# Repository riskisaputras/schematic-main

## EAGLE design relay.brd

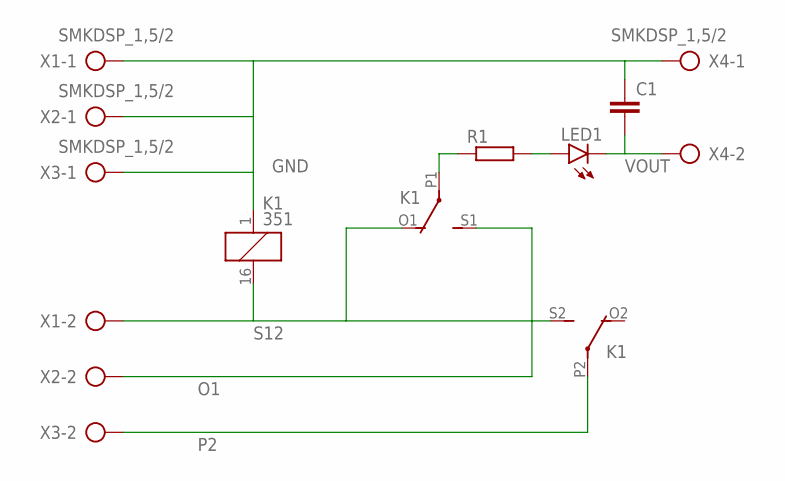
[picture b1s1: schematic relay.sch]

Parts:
C1: C-EU025-025X050; C025-025X050
K1: 351
LED1: LED3MM
R1: R-EU_0207/10; 0207/10
X1, X2, X3, X4: SMKDSP_1,5/2

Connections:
GND: C1.1, K1.1, X1.1, X2.1, X3.1, X4.1
unnamed: K1.P1, R1.1
unnamed: LED1.A, R1.2
O1: K1.S1 (S), X2.2
P2: K1.P2, X3.2
S12: K1.16 (2), K1.O1 (O), K1.S2 (S), X1.2
VOUT: C1.2, LED1.K (C), X4.2

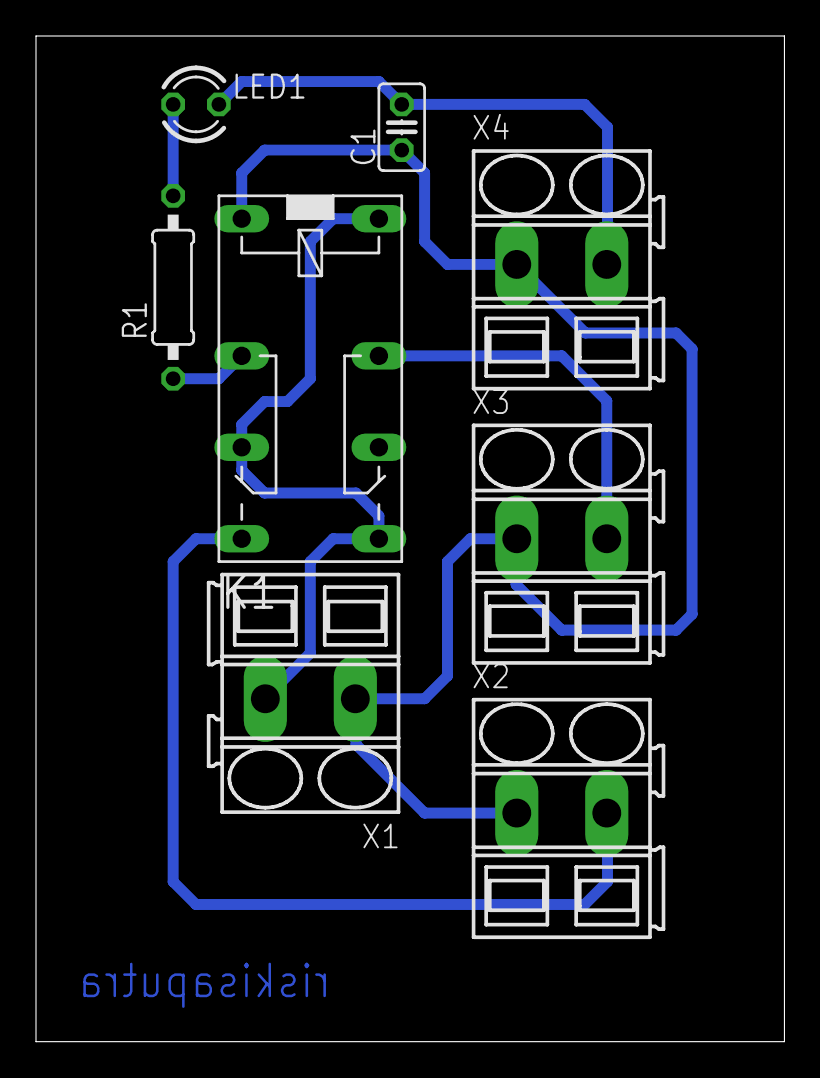
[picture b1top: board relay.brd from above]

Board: 2 copper layers, 41.6 x 55.9 mm, 8 parts (0 on the bottom side), 7 nets.

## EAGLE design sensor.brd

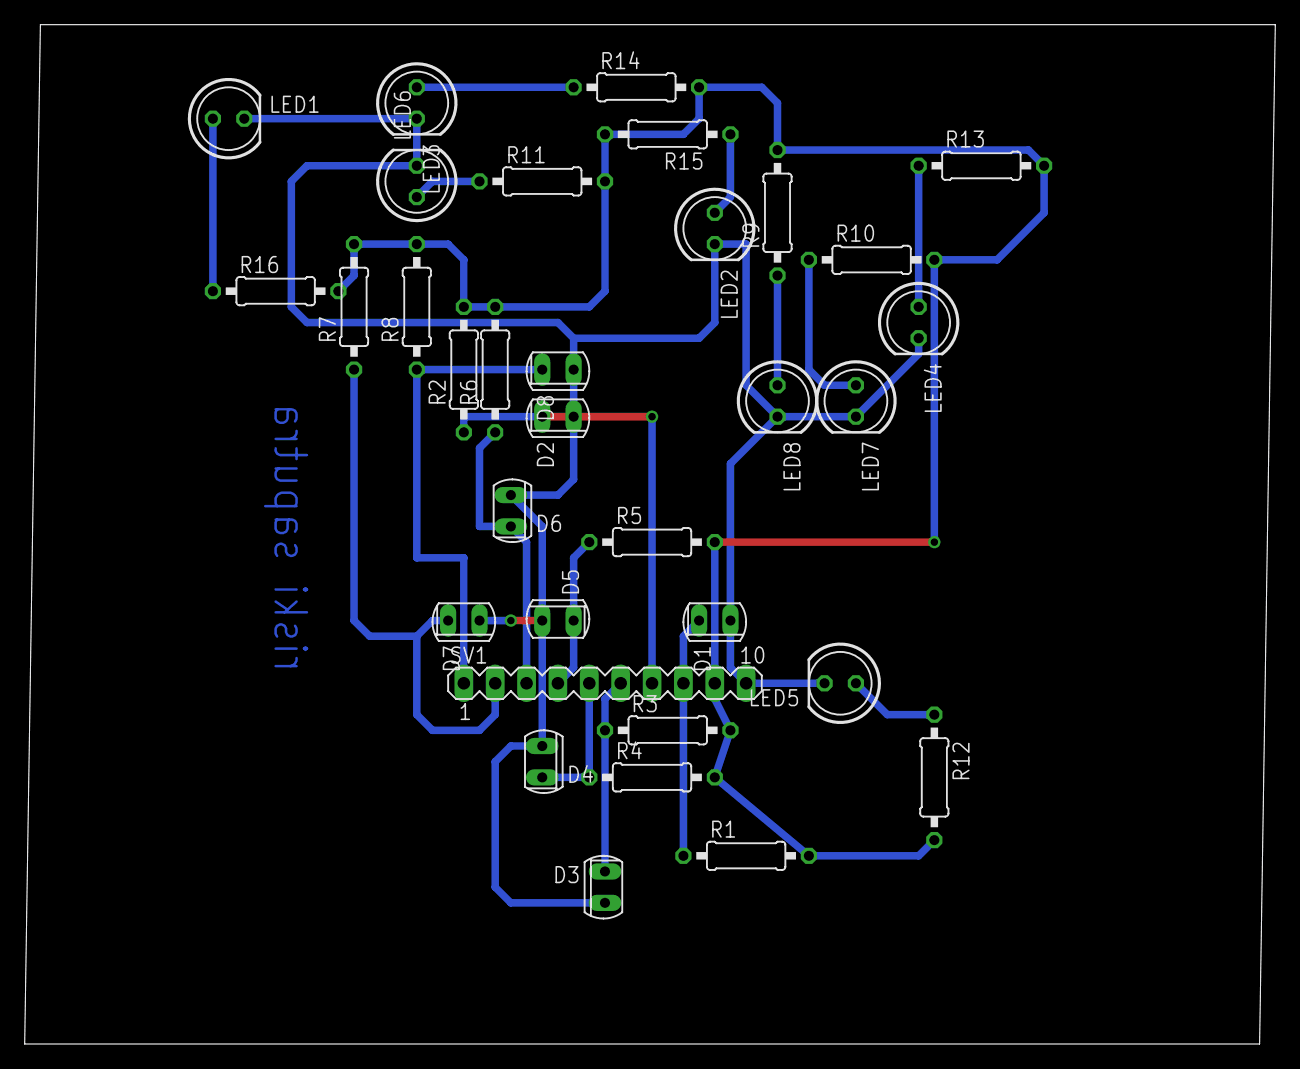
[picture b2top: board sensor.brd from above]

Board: 2 copper layers, 101.3 x 82.5 mm, 33 parts (0 on the bottom side), 18 nets.

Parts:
D1, D2, D3, D4, D5, D6, D7, D8: PhotoDioda; SFH225
LED1, LED2, LED3, LED4, LED5, LED6, LED7, LED8: LED putih SB; LED5MM
R1, R2, R3, R4, R5, R6, R7, R8: 0207/10
R9, R10, R11, R12, R13, R14, R15, R16: 330; 0207/10
SV1: MA10-1

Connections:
GND: D1.A, D2.A, D3.A, D4.A, D5.A, D6.A, D7.A, D8.A, LED1.K, LED2.K, LED3.K, LED4.K, LED5.K, LED6.K, LED7.K, LED8.K, SV1.10
unnamed: LED7.A, R10.1
unnamed: D7.K, R7.1, SV1.2
unnamed: D8.K, R8.1, SV1.1
unnamed: D1.K, R1.1, SV1.8
unnamed: D2.K, R2.1, SV1.7
unnamed: D3.K, R3.1, SV1.6
unnamed: D5.K, R5.1, SV1.4
unnamed: D4.K, R4.1, SV1.5
unnamed: D6.K, R6.1, SV1.3
unnamed: LED6.A, R11.1
unnamed: LED5.A, R12.1
unnamed: LED4.A, R13.1
unnamed: LED3.A, R14.1
unnamed: LED2.A, R15.1
unnamed: LED1.A, R16.1
unnamed: LED8.A, R9.1
VCC: R1.2, R2.2, R3.2, R4.2, R5.2, R6.2, R7.2, R8.2, R9.2, R10.2, R11.2, R12.2, R13.2, R14.2, R15.2, R16.2, SV1.9

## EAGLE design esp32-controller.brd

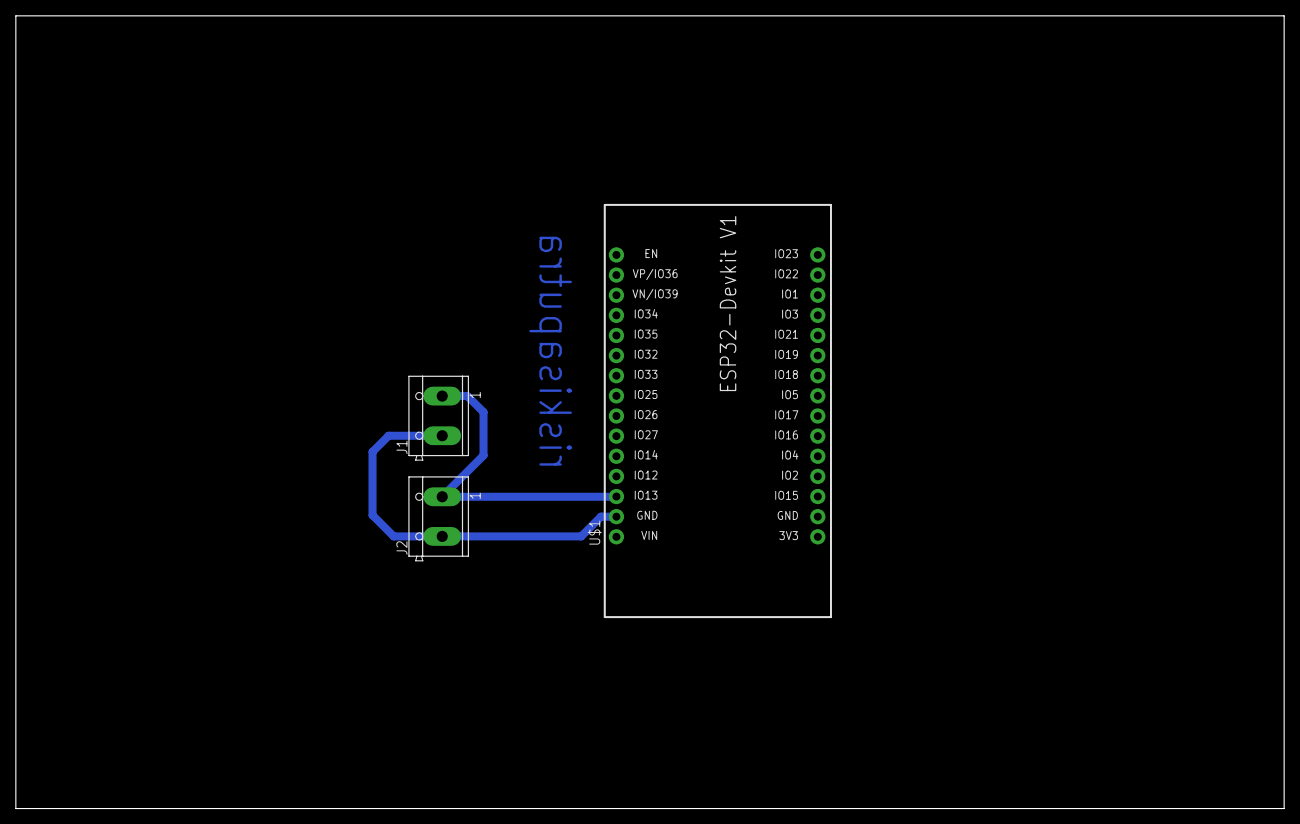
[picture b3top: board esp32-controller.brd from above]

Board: 2 copper layers, 160.0 x 100.0 mm, 3 parts (0 on the bottom side), 2 nets.

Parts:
J1, J2: CON_TERMINAL_BLOCK_02-5MM; TERMINAL_BLOCK_2P_5
U$1: ESP32DEVKITV1; ESP32-DEVKITV1

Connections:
GND: J1.1, J2.1, U$1.D13
HV: J1.2, J2.2, U$1.GND@1

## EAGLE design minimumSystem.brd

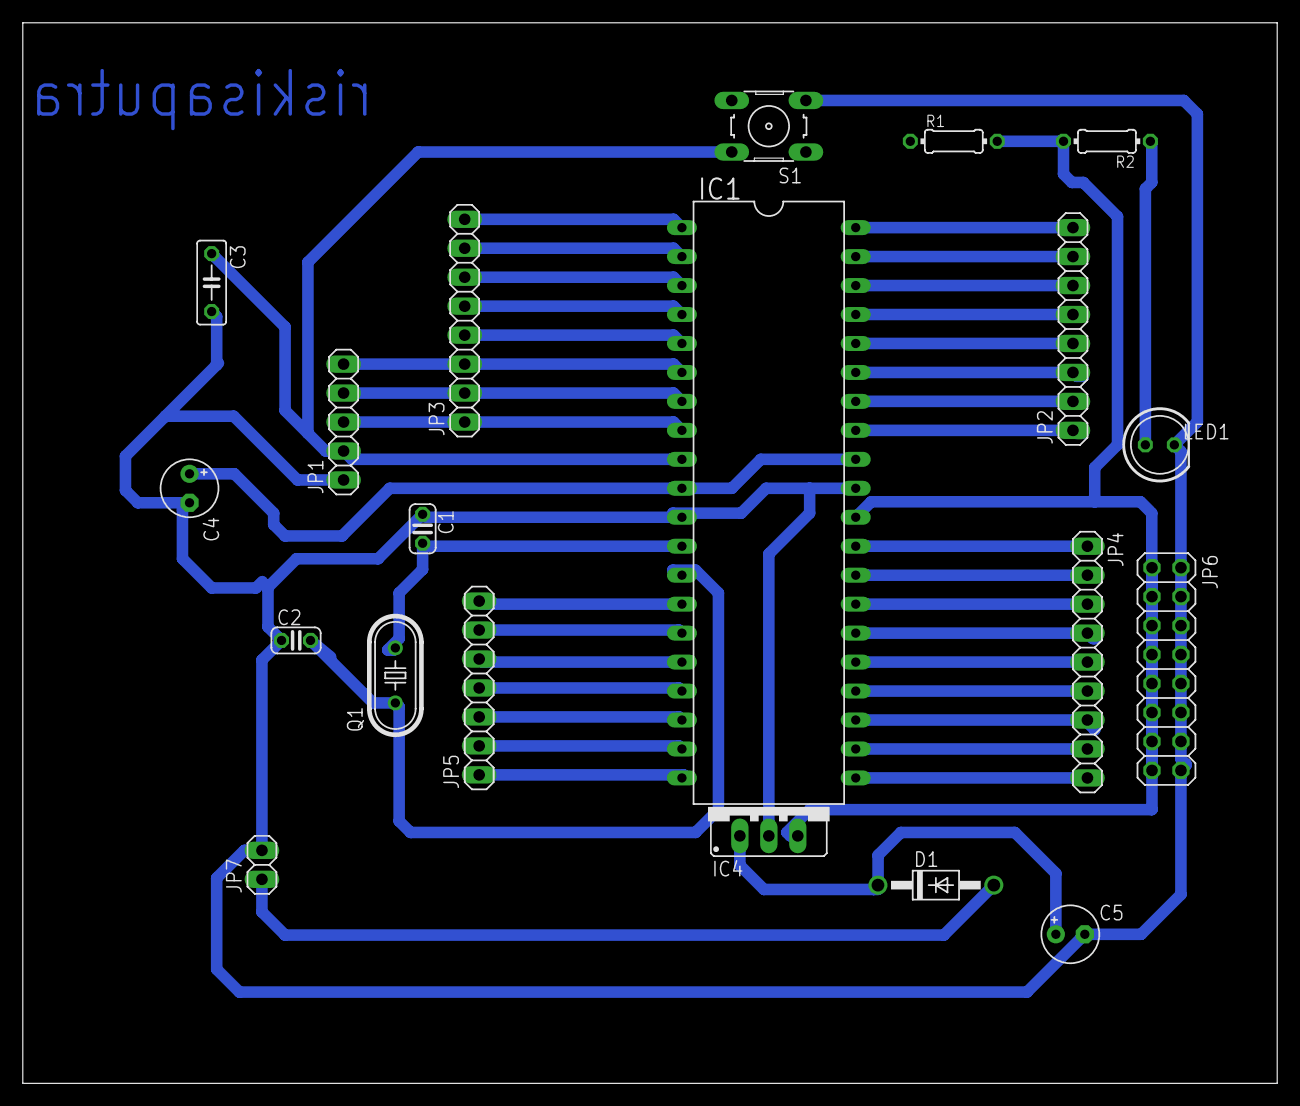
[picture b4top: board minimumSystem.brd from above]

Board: 2 copper layers, 110.0 x 93.0 mm, 20 parts (0 on the bottom side), 40 nets.

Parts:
C1, C2: C025-024X044
C3: C050-025X075
C4, C5: E2,5-5
D1: 1N4004; DO41-10
IC1: MEGA16-P; DIL40
IC4: 78XXS
JP1: 1X05
JP2, JP3: 1X08
JP4: 1X09
JP5: 1X07
JP6: 2X08
JP7: 1X02
LED1: LED5MM
Q1: HC49U-V
R1, R2: 0204/7
S1: B3F-10XX

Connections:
+5V: C4.+, IC1.10, IC1.30, IC1.32, IC4.OUT, JP6.1, JP6.3, JP6.5, JP6.7, JP6.9, JP6.11, JP6.13, JP6.15, R1.2, R2.2
+12V: D1.A, JP7.1
C0: IC1.22, JP4.8
C1: IC1.23, JP4.7
C2: IC1.24, JP4.6
C3: IC1.25, JP4.5
D7: IC1.14, JP5.7
GND: C1.1, C2.1, C3.2, C4.-, C5.-, IC1.11, IC1.31, IC4.GND, JP1.1, JP6.2, JP6.4, JP6.6, JP6.8, JP6.10, JP6.12, JP6.14, JP6.16, JP7.2, LED1.K, S1.3, S1.4
unnamed: IC1.33, JP2.1
unnamed: IC1.34, JP2.2
unnamed: IC1.35, JP2.3
unnamed: IC1.36, JP2.4
unnamed: IC1.37, JP2.5
unnamed: IC1.38, JP2.6
unnamed: IC1.39, JP2.7
unnamed: IC1.40, JP2.8
unnamed: IC1.29, JP4.1
unnamed: IC1.28, JP4.2
unnamed: IC1.27, JP4.3
unnamed: IC1.5, JP3.4
unnamed: IC1.20, JP5.1
unnamed: IC1.19, JP5.2
unnamed: IC1.26, JP4.4
unnamed: IC1.6, JP1.5, JP3.3
unnamed: IC1.4, JP3.5
unnamed: IC1.3, JP3.6
unnamed: IC1.2, JP3.7
unnamed: IC1.1, JP3.8
unnamed: C5.+, D1.C, IC4.IN
unnamed: IC1.15, JP5.6
unnamed: IC1.16, JP5.5
unnamed: IC1.17, JP5.4
unnamed: C3.1, IC1.9, JP1.2, S1.1, S1.2
unnamed: IC1.18, JP5.3
unnamed: C1.2, IC1.12, Q1.2
unnamed: C2.2, IC1.13, Q1.1
unnamed: LED1.A, R2.1
unnamed: IC1.8, JP1.3, JP3.1
unnamed: IC1.7, JP1.4, JP3.2
RS: IC1.21, JP4.9

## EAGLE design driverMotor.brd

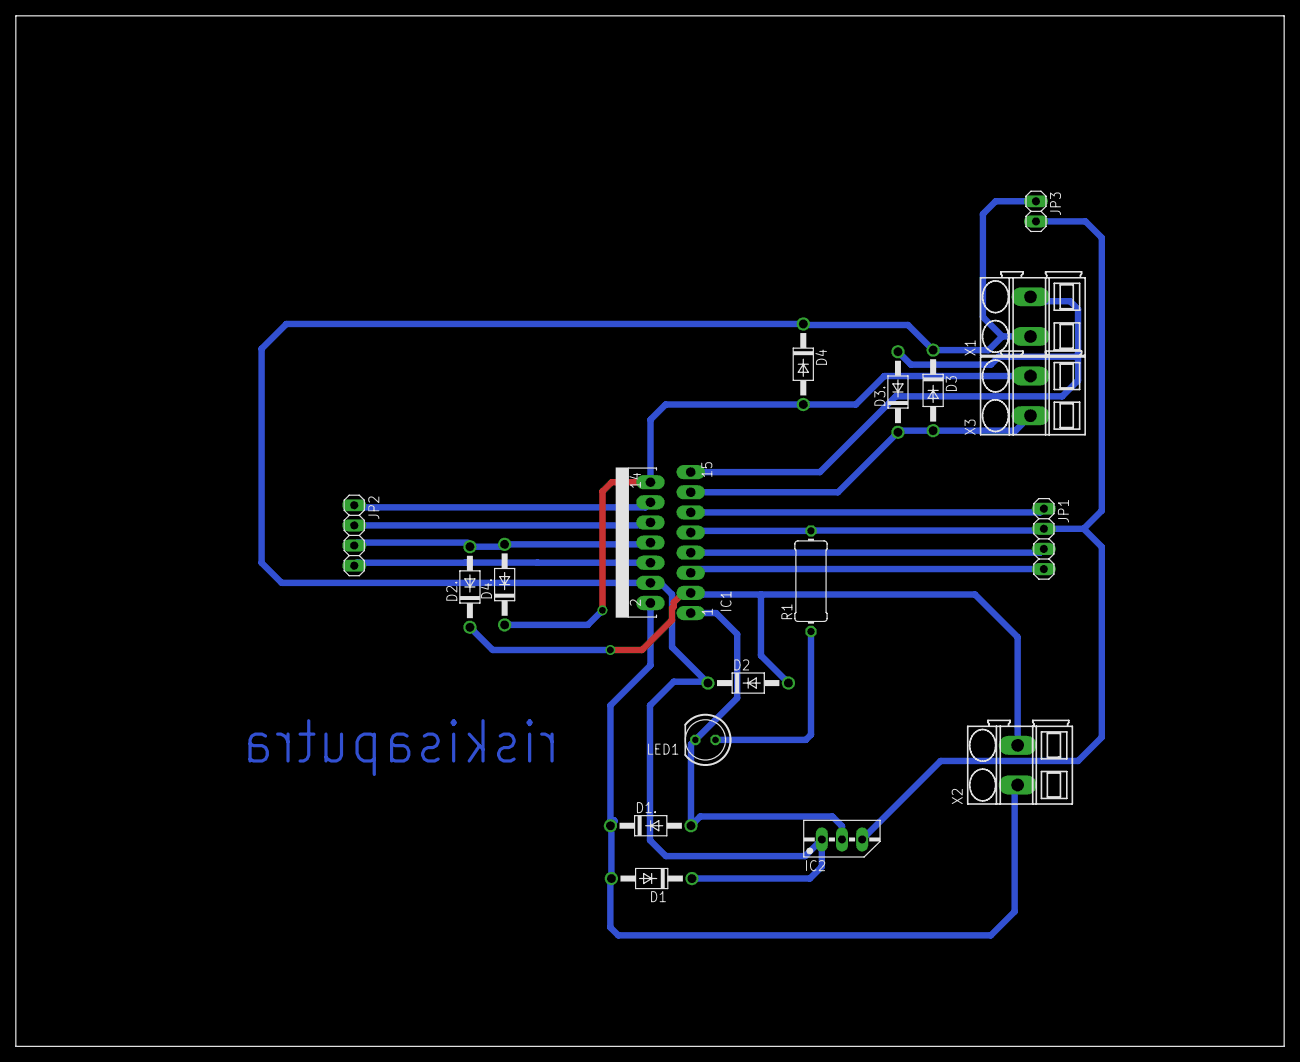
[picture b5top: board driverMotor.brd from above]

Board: 2 copper layers, 160.0 x 130.0 mm, 18 parts (0 on the bottom side), 14 nets.

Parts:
D1, D1., D2, D2., D3, D3., D4, D4.: 1N4004; DO41-10
IC1: L298; MULTIWATT-15
IC2: 78MXXS
JP1, JP2: 1X04
JP3: 1X02
LED1: LED5MM
R1: 0411/12
X1, X2, X3: SMKDSP_1,5/2

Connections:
+5V: IC1.9, IC2.OUT, JP1.2, JP3.2, R1.2
ENABLE_A: IC1.6, JP2.4
ENABLE_B: IC1.11, JP1.1
GND: D1..A, D2..A, D3..A, D4..A, IC1.1, IC1.8, IC1.15, IC2.GND, JP2.3, LED1.K, X1.2
INPUT1: IC1.5, JP1.4
INPUT2: IC1.7, JP1.3
INPUT3: IC1.10, JP2.2
INPUT4: IC1.12, JP2.1
LED: LED1.A, R1.1
MOTOR1_1: D1.A, D1..C, IC1.2, X2.1
MOTOR1_2: D2.A, D2..C, IC1.3, X2.2
MOTOR2_1: D3.A, D3..C, IC1.13, X3.1
MOTOR2_2: D4.A, D4..C, IC1.14, X3.2
VS: D1.C, D2.C, D3.C, D4.C, IC1.4, IC2.IN, JP3.1, X1.1

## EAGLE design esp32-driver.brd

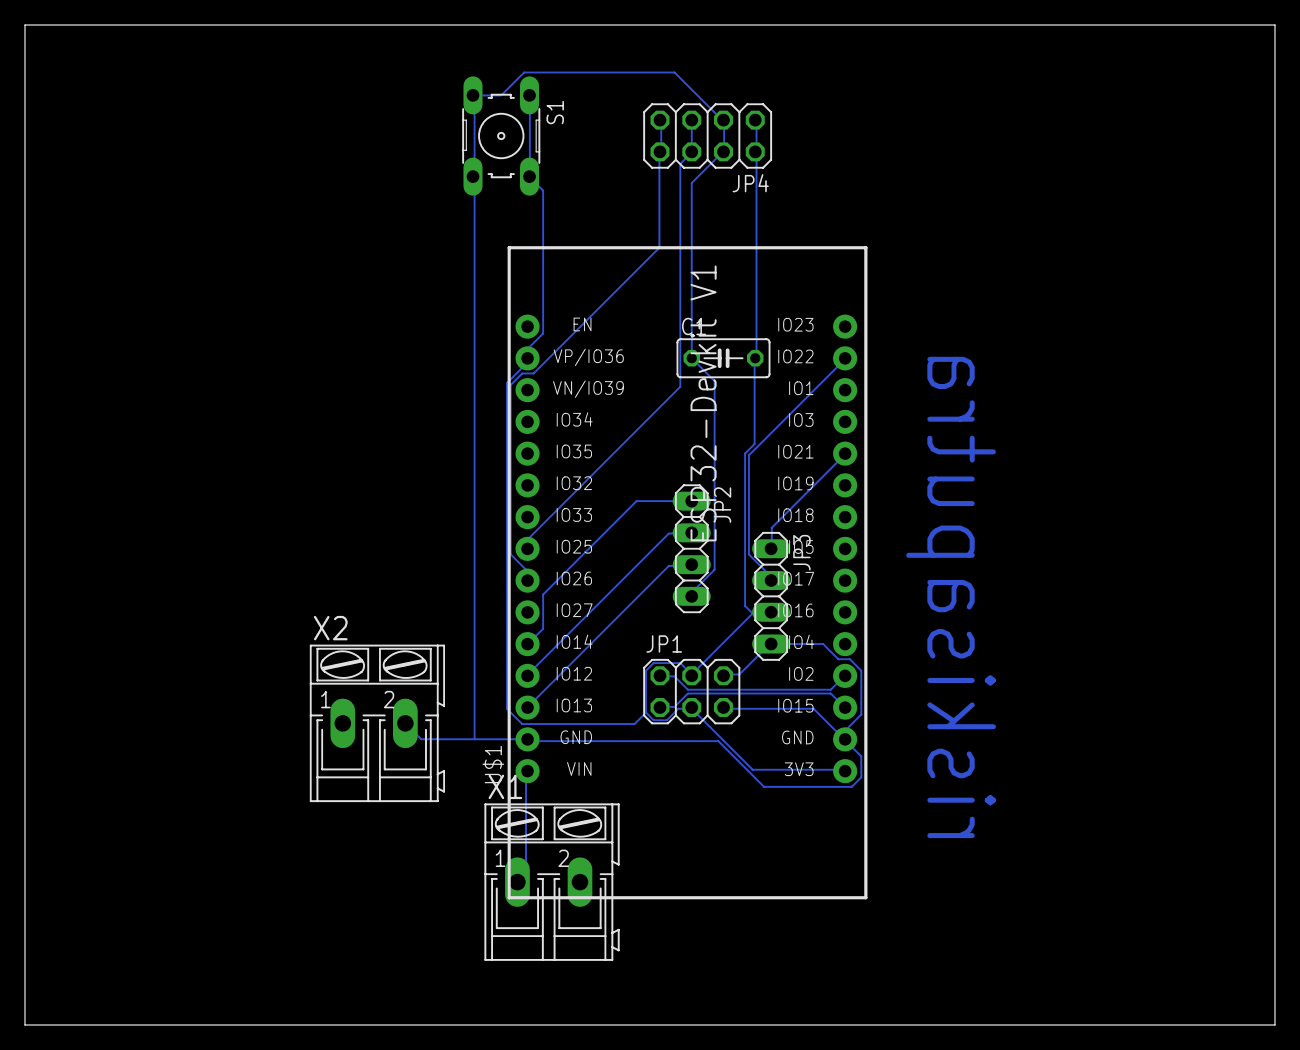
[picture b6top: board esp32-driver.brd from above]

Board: 2 copper layers, 100.0 x 80.0 mm, 9 parts (0 on the bottom side), 12 nets.

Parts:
C1: C050-030X075
JP1: 2X03
JP2, JP3: 1X04
JP4: 2X04
S1: B3F-10XX
U$1: ESP32DEVKITV1; ESP32-DEVKITV1
X1, X2: AK300/2

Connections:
GND: C1.1, JP1.5, JP1.6, JP2.4, JP3.4, JP4.3, JP4.4, S1.3, S1.4, U$1.GND@1, U$1.GND@2, X2.2
MOISTURE: JP1.2, U$1.D2
OUT1: JP2.1, U$1.D14
OUT2: JP2.2, U$1.D12
OUT3: JP2.3, U$1.D13
PH: JP1.1, U$1.D15
SCL: JP3.2, U$1.D22
SCL2: JP4.5, JP4.6, U$1.D25
SDA: JP3.1, U$1.D21
SDA2: JP4.7, JP4.8, U$1.D26
V: C1.2, JP1.3, JP1.4, JP3.3, JP4.1, JP4.2, S1.1, S1.2, U$1.3V3, U$1.D36
VIN: U$1.VIN, X1.1

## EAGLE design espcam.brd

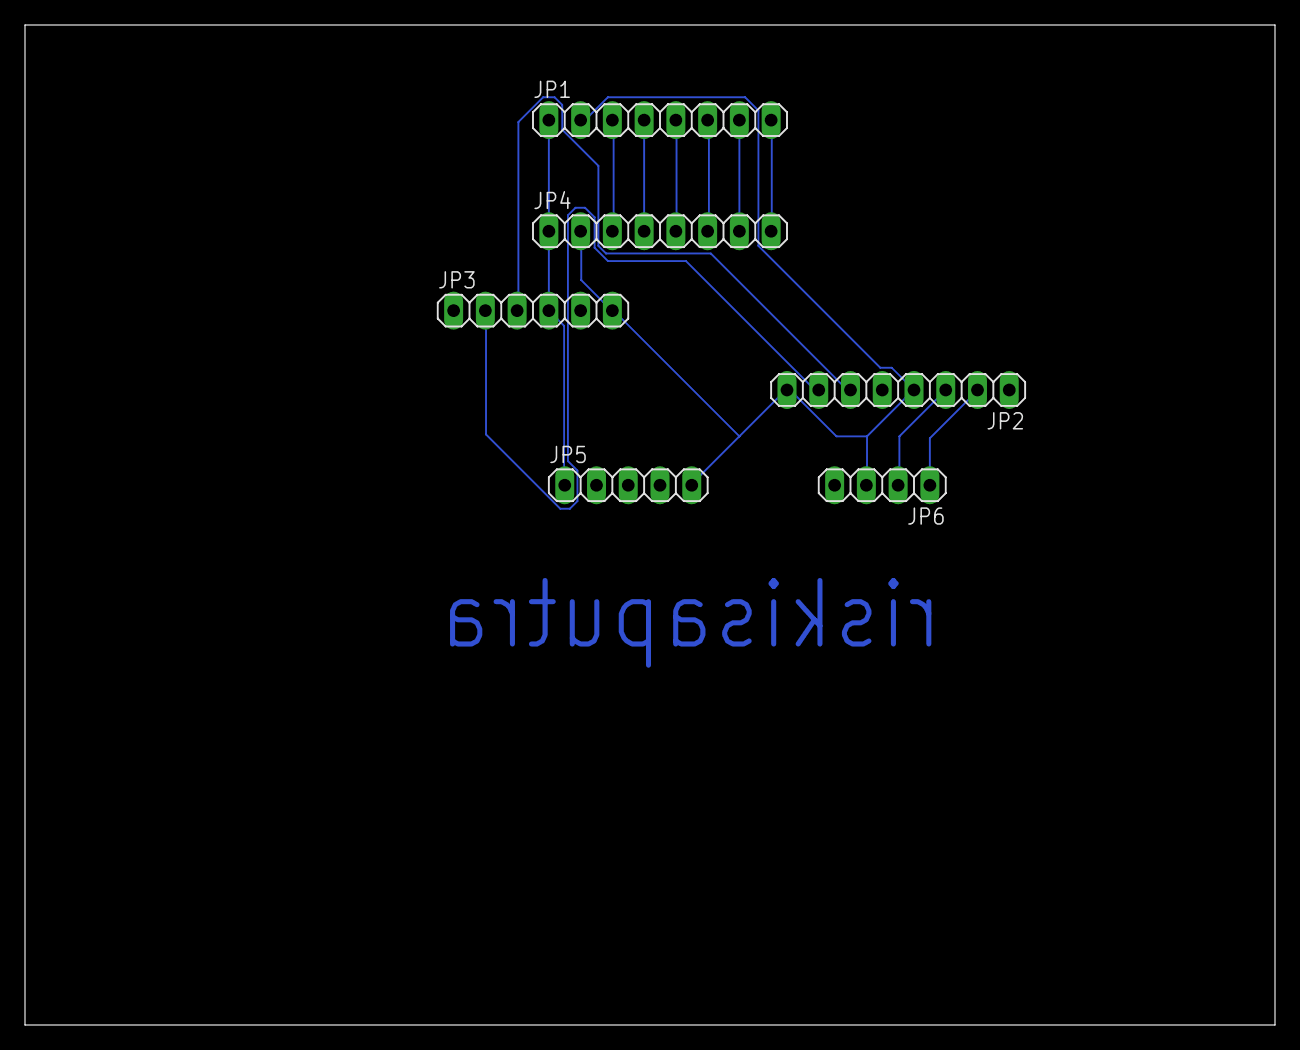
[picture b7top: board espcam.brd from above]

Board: 2 copper layers, 100.0 x 80.0 mm, 6 parts (0 on the bottom side), 13 nets.

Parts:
JP1, JP2, JP4: 1X08
JP3: 1X06
JP5: 1X05
JP6: 1X04

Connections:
5V: JP1.1, JP3.4, JP4.1, JP5.1
GND: JP1.2, JP2.4, JP2.8, JP3.6, JP4.2, JP5.5, JP6.3
IO0: JP2.3, JP6.2
IO2: JP1.7, JP4.7
IO4: JP1.8, JP4.8
IO12: JP1.3, JP4.3
IO13: JP1.4, JP4.4
IO14: JP1.6, JP4.6
IO15: JP1.5, JP4.5
IO16: JP2.2, JP6.1
RX: JP2.7, JP3.2
TX: JP2.6, JP3.3
VOUT: JP2.5, JP6.4

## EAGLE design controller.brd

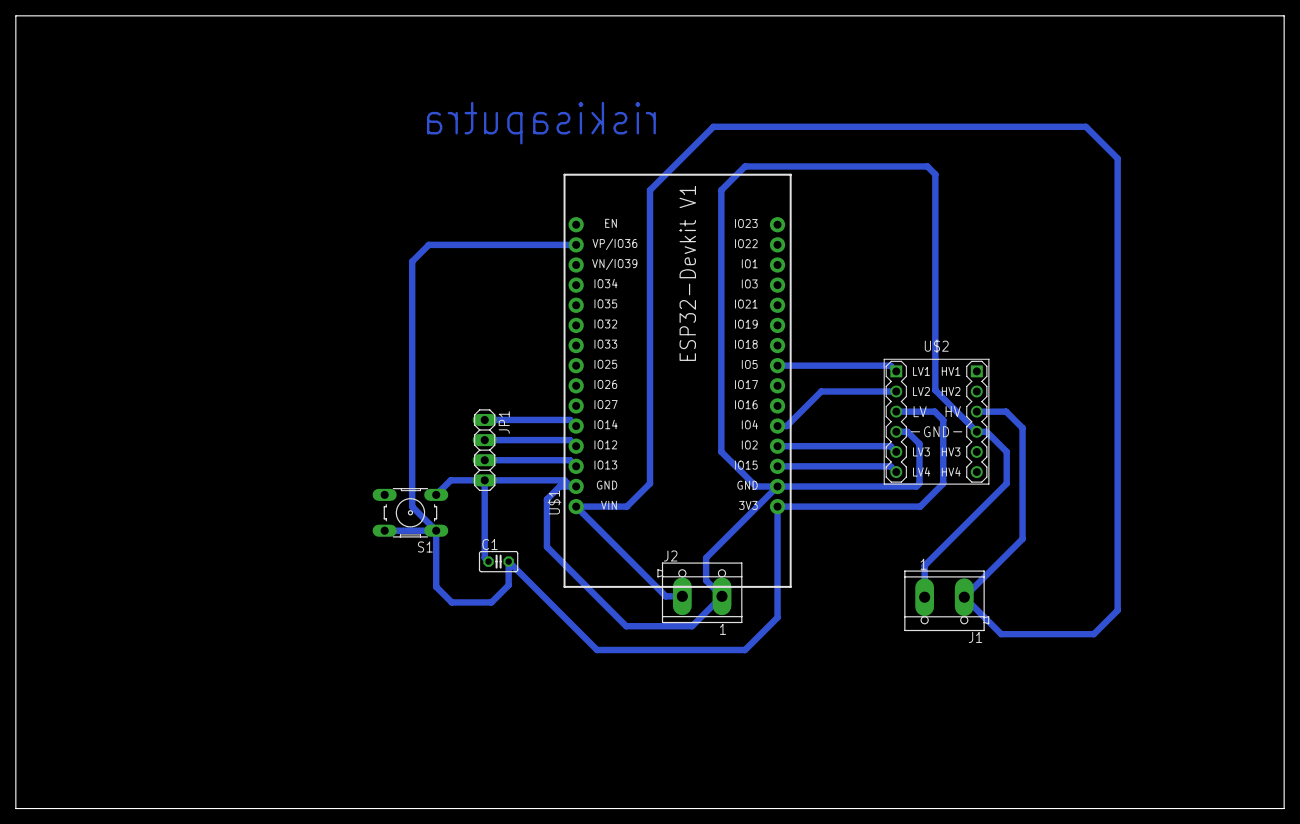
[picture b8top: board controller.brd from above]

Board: 2 copper layers, 160.0 x 100.0 mm, 7 parts (0 on the bottom side), 10 nets.

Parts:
C1: C025-025X050
J1, J2: CON_TERMINAL_BLOCK_02-5MM; TERMINAL_BLOCK_2P_5
JP1: 1X04
S1: B3F-10XX
U$1: ESP32DEVKITV1; ESP32-DEVKITV1
U$2: LEVEL-SHIFTER-4CH

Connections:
GND: C1.1, J1.1, J2.1, JP1.4, S1.3, S1.4, U$1.GND@1, U$1.GND@2, U$2.J1.4, U$2.J2.4
HV: J1.2, J2.2, U$1.VIN, U$2.J2.3
LV: C1.2, S1.1, S1.2, U$1.3V3, U$1.D36, U$2.J1.3
LV1: U$1.D5, U$2.J1.1
LV2: U$1.D4, U$2.J1.2
LV3: U$1.D2, U$2.J1.5
LV4: U$1.D15, U$2.J1.6
OUT1: JP1.1, U$1.D14
OUT2: JP1.2, U$1.D12
OUT3: JP1.3, U$1.D13

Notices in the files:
parts and their libraries:
diy-model: Released under the Creative Commons Attribution 4.0 International License: http://creativecommons.org/licenses/by/4.0
